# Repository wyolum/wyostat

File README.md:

# wyostat
Open source thermostat

* install node-red
           * https://nodered.org/docs/hardware/raspberrypi
* install node-red-dashboard
   	   * (from the ~/.node-red)
	   * https://flows.nodered.org/node/node-red-dashboard
* install node-red start up trigger: npm install node-red-contrib-startup-trigger
* install mosquitto (steps 1 & 2
           *https://learn.adafruit.com/diy-esp8266-home-security-with-lua-and-mqtt/configuring-mqtt-on-the-raspberry-pi)
* start node-red (from the command-line type $node-red)
* start mosquitto (from the command line type $moquitto)
* edit OpenThermostat.json from within node-red (update mqtt-broker ip address)
* deploy OpenThermostat.json from within node-red (update mqtt-broker ip address)
* Copy and edit arduino/OpenThermostat/README to arduino/OpenThermostat/config.h
* upload OpenThermostat.ino

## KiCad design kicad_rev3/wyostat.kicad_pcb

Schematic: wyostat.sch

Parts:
C1, C3, C5: 10nF,120V; C_1210
C7: 100nF; C_0805
C9: 100nF,100V; C_0805
C10: 100uF,50V; CP_Elec_10x10
C11: 2.2uF,50V; C_0805
C12: 1uF; C_0805
C13: 3.3nF; C_0805
C14: 10uF; C_0805
C15: 4.7uF; C_0805
D1, D2, D3: LED; LED_0603
D4: DiodeBridge; Diode_bridge
D5: CDSOD323-T05L; D_SOD-323_HandSoldering
F1: Polyfuse; Fuse_SMD2920
J1: 24 V AC IN; TerminalBlock_Pheonix_MPT-2.54mm_2pol
J2: OUT1; TerminalBlock_Pheonix_MPT-2.54mm_2pol
J3: OUT2; TerminalBlock_Pheonix_MPT-2.54mm_2pol
J4: OUT3; TerminalBlock_Pheonix_MPT-2.54mm_2pol
J5: I2C_ext1; Pin_Header_TMP102_1x06
J6: RH; pad_rect_smd
J7: RC; pad_rect_smd
J8: C; pad_rect_smd
J9: Y1; pad_rect_smd
J10: Y2; pad_rect_smd
J11: G; pad_rect_smd
J12: W1; pad_rect_smd
J13: USB_microAB; USB_Micro-B_Molex-105017-0001
J14: W2; pad_rect_smd
J15: Conn_Spare; TerminalBlock_Pheonix_MPT-2.54mm_3pol
J16: 5V_SEL; Pin_Header_Straight_1x04
JP1, JP2, JP3: LED_en; R_0805
JP4: GND; LED_0402
L1: 22uH; Inductor_ELL8TP
L2, L4: 330E; R_0805
Logo1: LOGO_WL; logo-WL3
Logo2: OSHW; logo-OSHW_6mm
Logo3: KiCad; logo-kicad_6mm_SilkScreen
Logo4: logo_snb; logo-skull_n_bones
Logo5: logo_warning; logo-warning
Q1, Q2, Q3: BTA204S; DPAK-2
R1, R5, R7, R12, R13, R17: 360; R_0805
R3, R9, R15: 200; R_0805
R4, R10, R16: 300; R_0805
R6, R11, R18: 39; R_0805
R19, R20, R21, R22: 10k; R_0805
R23, R24, R25: 0E; R_0805
S1: SW-ENTER; SW_SPST_FSM6JSMA
S2: SW-INC; SW_SPST_FSM6JSMA
S3: SW-DEC; SW_SPST_FSM6JSMA
S4: SW-MODE; SW_SPST_FSM6JSMA
SC1, SC2, SC3, SC4: SCREW; MountingHole_3.2mm_M3_Pad_Via
U1, U2, U3: MOC3063M; Optocoupler_6pin_smd
U4: Wemos-Lolin; Wemos_Lolin
U5: MAX17502FATB+T; TDFN-10

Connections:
/3V3: C7.2, J5.2, S1.1, S1.3, S2.1, S2.3, S3.1, S3.3, S4.2, S4.4, U4.13, U4.19; also elsewhere on the board
/5V: J16.2, J16.3, U4.16, U4.17
/5V_EXT: C14.1, J16.4, L1.2, U5.5
/5V_USB: C15.1, J16.1, L2.1
/24Vac-C: D4.3, J1.2, J2.2, J3.2, J4.2, J8.1
/24Vac-H: C1.2, C3.2, C5.2, F1.2, J1.1, J6.1, Q1.2 (T2), Q2.2 (T2), Q3.2 (T2), R1.2, R7.2, R13.2
/40VDC: C9.1, C10.1, C11.2, D4.1, U5.2, U5.3
/D+: J13.3, R24.2
/D-: J13.2, R23.2
/ID: J13.4, R25.2
/IN1: D1.1, U1.1, U4.24
/IN2: D2.1, U2.1, U4.25
/IN3: D3.1, U3.1, U4.2
/LX: L1.1, U5.10
/OUT1: J2.1, J9.1, Q1.1 (T1), R5.2, R6.1
/OUT2: J3.1, J11.1, Q2.1 (T1), R11.1, R12.2
/OUT3: J4.1, J12.1, Q3.1 (T1), R17.2, R18.1
/RC: J7.1, J15.2
/SCL: J5.4, U4.4; also elsewhere on the board
/SDA: J5.3, U4.3; also elsewhere on the board
/SS: C13.2, U5.6
/SW_D: R21.1, S3.2, S3.4, U4.8
/SW_E: R19.1, S1.2, S1.4, U4.9
/SW_I: R20.1, S2.2, S2.4, U4.10
/SW_M: R22.1, S4.1, S4.3, U4.7
/USB+: D5.1 (K), J13.1, L2.2
/VCC: C12.1, U5.4
/W2: J14.1, J15.1
/Y2: J10.1, J15.3
GND: C7.1, C9.2, C10.2, C11.1, C12.2, C13.1, C14.2, C15.2, D4.2, D5.2 (A), J5.1, J13.5, JP1.2, JP2.2, JP3.2, JP4.1, JP4.2, L4.2, R4.1, R10.1, R16.1, R19.2, R20.2, R21.2, R22.2, U4.14, U4.15, U4.18, U5.1, U5.9, U5.11; also elsewhere on the board
unnamed: C1.1, R6.2
unnamed: C3.1, R11.2
unnamed: C5.1, R18.2
unnamed: D1.2, R3.2
unnamed: D2.2, R9.2
unnamed: D3.2, R15.2
unnamed: D4.4, F1.1
unnamed: J13.S1, J13.S2, J13.S3, J13.S4, L4.1
unnamed: JP1.1, R3.1
unnamed: JP2.1, R9.1
unnamed: JP3.1, R15.1
unnamed: Q1.3 (G), R5.1, U1.4
unnamed: Q2.3 (G), R12.1, U2.4
unnamed: Q3.3 (G), R17.1, U3.4
unnamed: R1.1, U1.6
unnamed: R4.2, U1.2
unnamed: R7.1, U2.6
unnamed: R10.2, U2.2
unnamed: R13.1, U3.6
unnamed: R16.2, U3.2

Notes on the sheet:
Push Buttons
I2C interface for external connections to sensors etc. Sparkfun TMP102 breakout P/N : 13314 https://www.sparkfun.com/products/13314
I2C HEADER
TRIAC outputs
1.5V
Connect GNDREF to GND at VCC capacitor
AC-DC POWER SUPPLY
40 V AC MAX. ISOLATED
40 V AC MAX
INPUT POWER Input Power sources are : a. Micro USB 5V to Wemos Lolin b. 28 V AC to 5 V DC via switching regulator c. Micro USB on Wyostat (only Power, no Data) When using option "b" or "c", the micro USB cable MUST be removed to prevent power conflicts. When using option "a", the Power Selector Hea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
USB INPUT + REGULATOR
5mA
I2C RTC
24VAC MAX., ISOLATED DO NOT CONNECT 115VAC
USB OFF EXT
Extra connection pads brokenout to screw connector

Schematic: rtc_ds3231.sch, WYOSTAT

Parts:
BT1: Batt_RTC; CR2032_SMD2; Digikey BU2032SM-HD-GCT-ND
C8: 100nF; C_0805
R26, R27: 10k; R_0805
R28, R29: 4K7; R_0805
TP1: ~RST; Pin_Header_Straight_1x01
TP2: SQR; Pin_Header_Straight_1x01
TP3: 32kHz; Pin_Header_Straight_1x01
U6: DS3231N; DS3231

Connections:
/3V3: R26.1, R27.1, R28.2, R29.2, U6.2; also elsewhere on the board
/SCL: R28.1, U6.16; also elsewhere on the board
/SDA: R29.1, U6.15; also elsewhere on the board
/rtc_ds3231/32kHz: R27.2, TP3.1, U6.1
/rtc_ds3231/BAT: BT1.1, C8.1, U6.14
/rtc_ds3231/RESET: TP1.1, U6.4
/rtc_ds3231/SQR: R26.2, TP2.1, U6.3
GND: BT1.2, C8.2, U6.5, U6.6, U6.7, U6.8, U6.9, U6.10, U6.11, U6.12, U6.13; also elsewhere on the board

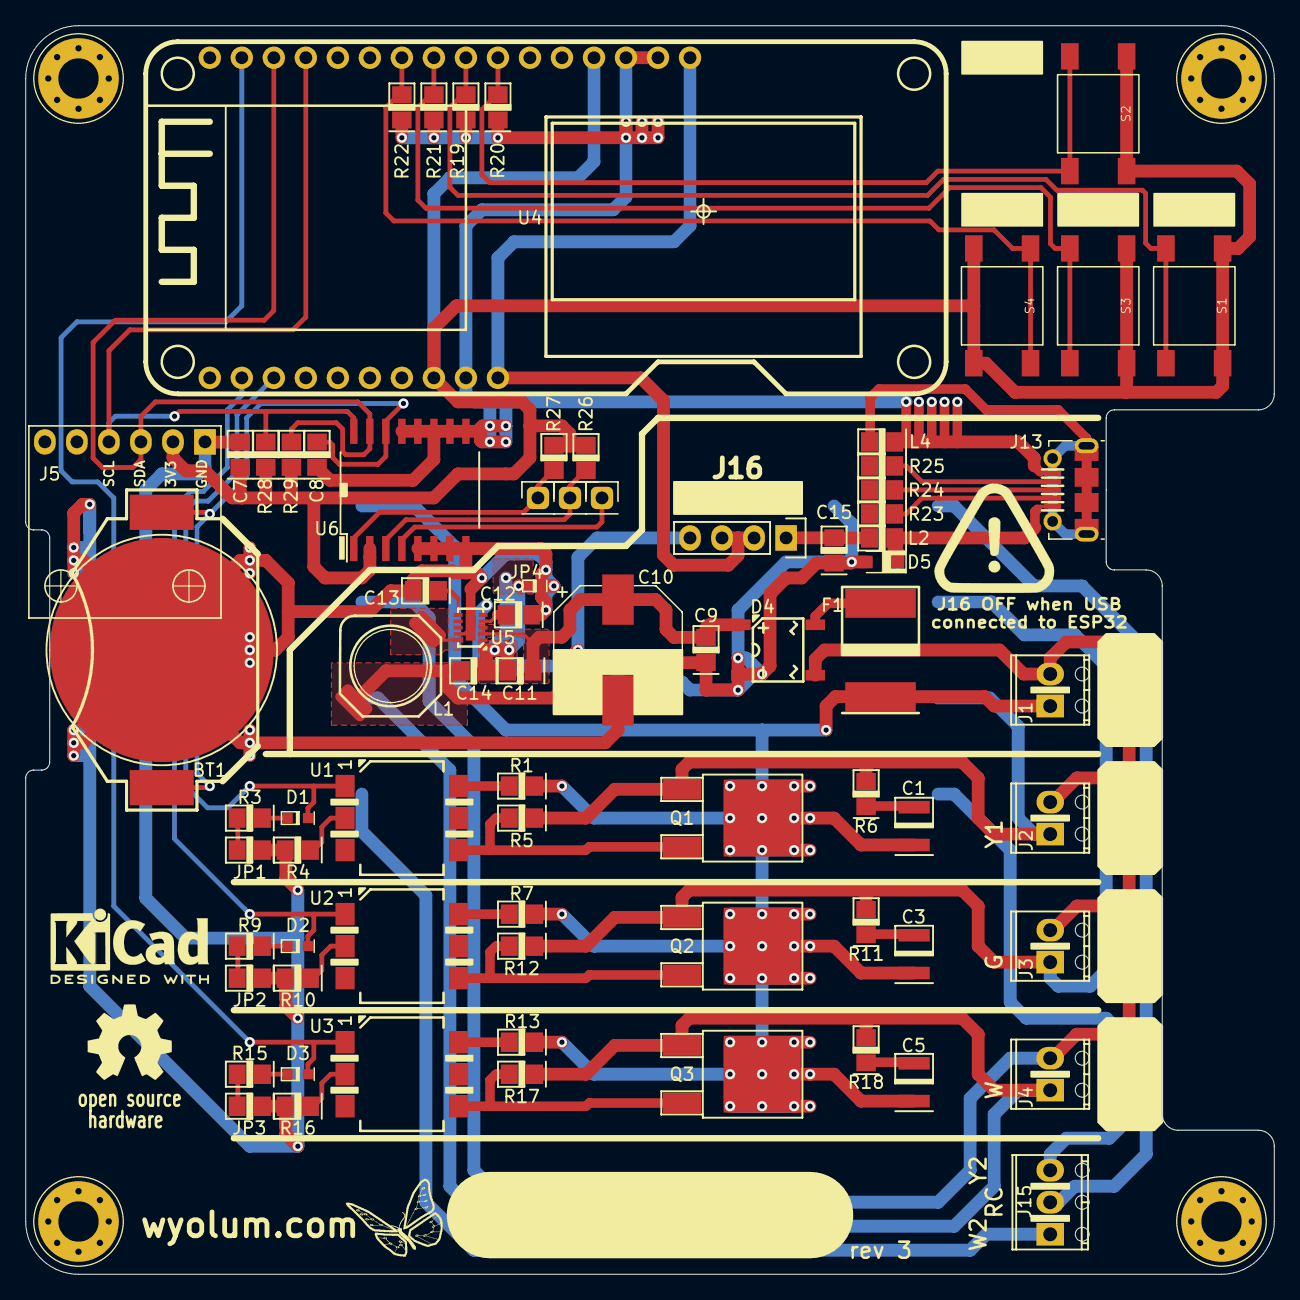
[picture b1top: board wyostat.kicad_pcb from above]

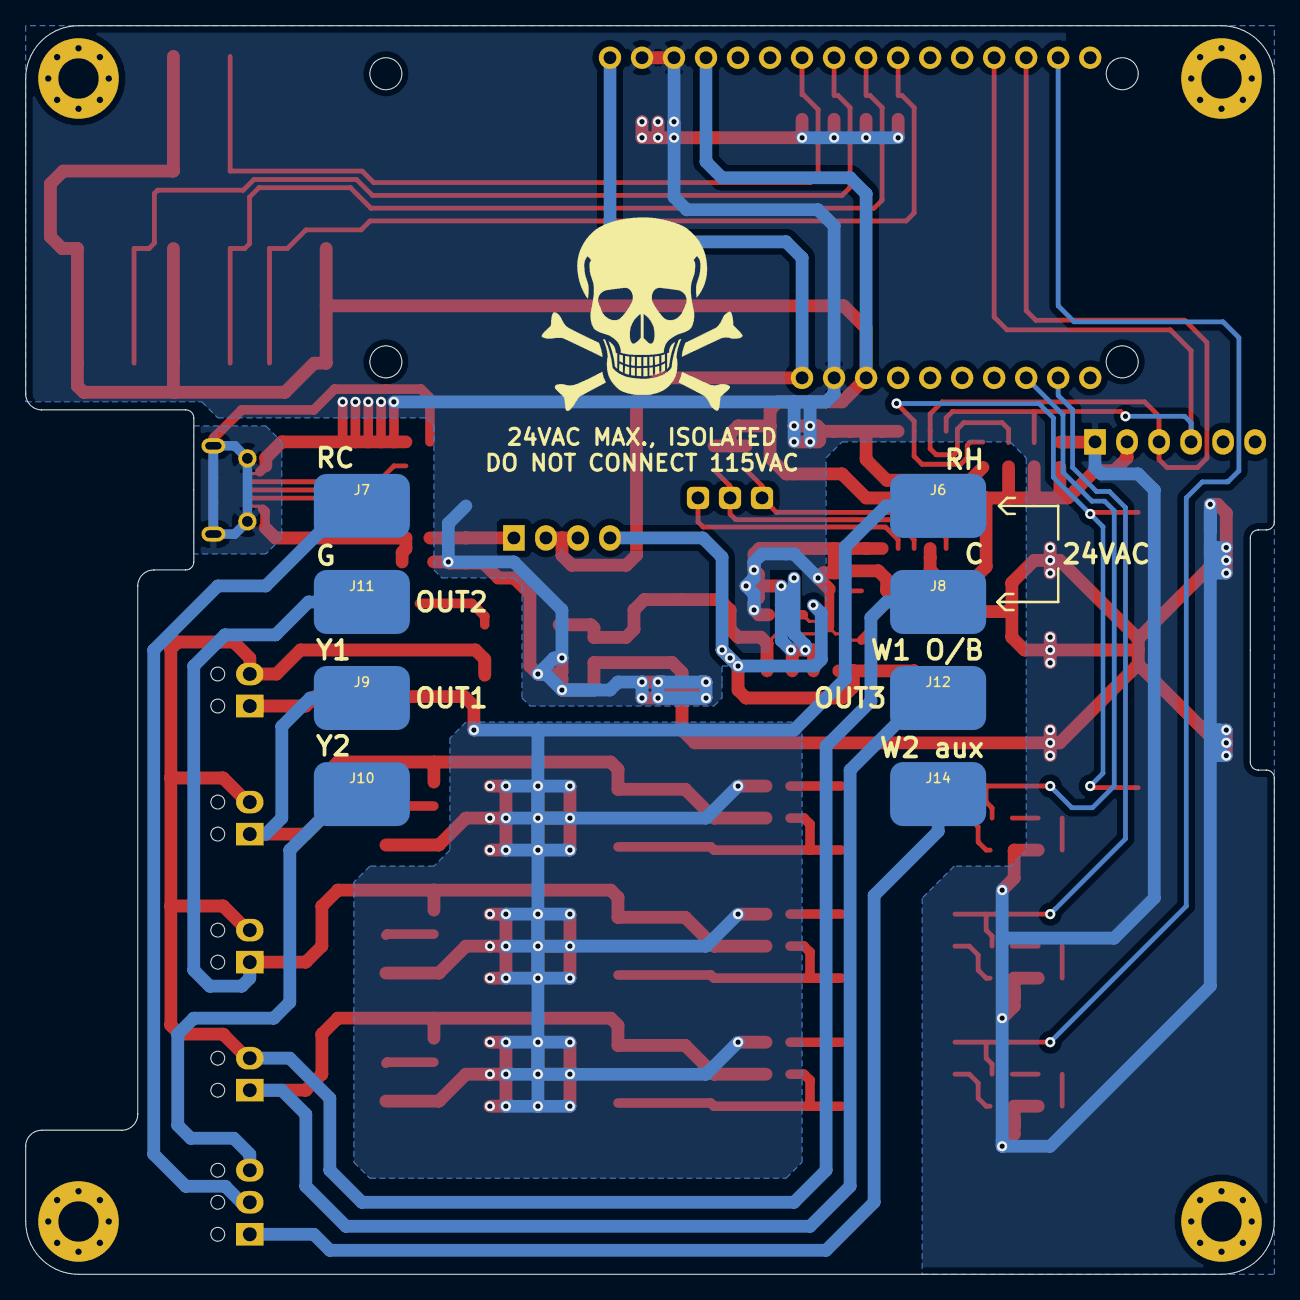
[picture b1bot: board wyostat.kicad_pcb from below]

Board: 2 copper layers, 99.1 x 99.1 mm, 93 parts (9 on the bottom side), 54 nets.

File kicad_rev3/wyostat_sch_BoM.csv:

Reference Type, Quantity, Reference, Value, Footprint, Datasheet, manf#, Field4, Field5, Field6, Field7, Field8, Field9, Field10, Field11, DNP, Digikey
"BT","1","BT1,","Batt_RTC","wyostat_fp:CR2032_SMD2","","mfr_pn","","","","","","","","","","BU2032SM-HD-GCT-ND "
"C","1","C13,","3.3nF","wyostat_fp:C_0805",""
"C","2","C7,C8,","100nF","wyostat_fp:C_0805",""
"C","1","C9,","100nF,100V","wyostat_fp:C_0805","","mfr_pn","","","","","","","","","",""
"C","3","C1,C3,C5,","10nF,120V","wyostat_fp:C_1210",""
"C","1","C12,","1uF","wyostat_fp:C_0805",""
"C","1","C15,","4.7uF","wyostat_fp:C_0805","","Value","","","","","","","","","",""
"C","1","C14,","10uF","wyostat_fp:C_0805",""
"C","1","C11,","2.2uF,50V","wyostat_fp:C_0805",""
"C","1","C10,","100uF,50V","wyostat_fp:CP_Elec_10x10",""
"D","1","D5,","CDSOD323-T05L","wyostat_fp:D_SOD-323_HandSoldering",""
"D","1","D4,","DiodeBridge","wyostat_fp:Diode_bridge",""
"D","3","D1,D2,D3,","LED","wyostat_fp:LED_0603","","","LED SS 5MM 625NM RED DIFF","2V, 10mA","Round with Domed Top, 5mm, T-1 3/4","Kingbright Corp","WP7113ID","Digikey","754-1264-ND","http://www.digikey.com/product-detail/en/WP7113ID/754-1264-N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","",""
"F","1","F1,","Polyfuse","wyostat_fp:Fuse_SMD2920",""
"J","1","J1,","24 V AC IN","wyostat_fp:TerminalBlock_Pheonix_MPT-2.54mm_2pol","","Value","","","","","","","","","",""
"J","1","J8,","C","wyostat_fp:pad_rect_smd",""
"J","1","J15,","Conn_Spare","wyostat_fp:TerminalBlock_Pheonix_MPT-2.54mm_3pol",""
"J","1","J11,","G","wyostat_fp:pad_rect_smd",""
"J","1","J5,","I2C_ext1","wyostat_fp:Pin_Header_Straight_1x04",""
"J","1","J2,","OUT1","wyostat_fp:TerminalBlock_Pheonix_MPT-2.54mm_2pol","","Value","","","","","","","","","",""
"J","1","J3,","OUT2","wyostat_fp:TerminalBlock_Pheonix_MPT-2.54mm_2pol","","Value","","","","","","","","","",""
"J","1","J4,","OUT3","wyostat_fp:TerminalBlock_Pheonix_MPT-2.54mm_2pol","","Value","","","","","","","","","",""
"J","1","J7,","RC","wyostat_fp:pad_rect_smd",""
"J","1","J6,","RH","wyostat_fp:pad_rect_smd",""
"J","1","J13,","USB_microAB","wyostat_fp:USB_Micro-B_Molex-105017-0001","","Value","","","","","","","","","",""
"J","1","J16,","5V_SEL","wyostat_fp:Pin_Header_Straight_1x04",""
"J","1","J12,","W1","wyostat_fp:pad_rect_smd",""
"J","1","J14,","W2","wyostat_fp:pad_rect_smd",""
"J","1","J9,","Y1","wyostat_fp:pad_rect_smd",""
"J","1","J10,","Y2","wyostat_fp:pad_rect_smd",""
"JP","1","JP4,","GND","wyostat_fp:LED_0402",""
"JP","3","JP1,JP2,JP3,","LED_en","wyostat_fp:R_0805",""
"L","2","L4,L2,","330E","wyostat_fp:R_0805","","Value","","","","","","","","","",""
"L","1","L1,","22uH","wyostat_fp:Inductor_ELL8TP","","mfr_pn","","","","","","","","","",""
"Logo","1","Logo3,","KiCad","wyostat_fp:logo-kicad_6mm_SilkScreen","","Value","","","","","","","","","",""
"Logo","1","Logo1,","LOGO_WL","wyostat_fp:logo-WL3","","Value","","","","","","","","","",""
"Logo","1","Logo2,","OSHW","wyostat_fp:logo-OSHW_6mm","","Value","","","","","","","","","",""
"Logo","1","Logo4,","logo_snb","wyostat_fp:logo-skull_n_bones","","Value","","","","","","","","","",""
"Logo","1","Logo5,","logo_warning","wyostat_fp:logo-warning","","Value","","","","","","","","","",""
"Q","3","Q1,Q2,Q3,","BTA204S","wyostat_fp:DPAK-2",""
"R","3","R6,R11,R18,","39","wyostat_fp:R_0805","","Value","","","","","","","","","-",""
"R","3","R3,R9,R15,","200","wyostat_fp:R_0805","","Value","","","","","","","","","",""
"R","3","R4,R10,R16,","300","wyostat_fp:R_0805","","Value","","","","","","","","","",""
"R","6","R1,R7,R13,R5,R12,R17,","360","wyostat_fp:R_0805","","Value","","","","","","","","","",""
"R","3","R23,R24,R25,","0E","wyostat_fp:R_0805","","Value","","","","","","","","","DNP",""
"R","2","R28,R29,","4K7","wyostat_fp:R_0805","","mfr_pn","","","","","","","","","",""
"R","6","R21,R22,R19,R20,R26,R27,","10k","wyostat_fp:R_0805",""
"S","1","S3,","SW-DEC","wyostat_fp:SW_SPST_FSM6JSMA",""
"S","1","S1,","SW-ENTER","wyostat_fp:SW_SPST_FSM6JSMA",""
"S","1","S2,","SW-INC","wyostat_fp:SW_SPST_FSM6JSMA",""
"S","1","S4,","SW-MODE","wyostat_fp:SW_SPST_FSM6JSMA",""
"SC","4","SC1,SC2,SC3,SC4,","SCREW","wyostat_fp:MountingHole_3.2mm_M3_Pad_Via",""
"TP","1","TP2,","SQR","wyostat_fp:Pin_Header_Straight_1x01","","mfr_pn","","","","","","","","","",""
"TP","1","TP3,","32kHz","wyostat_fp:Pin_Header_Straight_1x01","","mfr_pn","","","","","","","","","",""
"TP","1","TP1,","~RST","wyostat_fp:Pin_Header_Straight_1x01","","mfr_pn","","","","","","","","","",""
"U","1","U6,","DS3231N","wyostat_fp:DS3231","","mfr_pn","","","","","","","","","",""
"U","1","U5,","MAX17502FATB+T","wyostat_fp:TDFN-10","","mfr_pn","","","","","","","","","",""
"U","3","U1,U2,U3,","MOC3063M","wyostat_fp:Optocoupler_6pin_smd",""
"U","1","U4,","Wemos-Lolin","wyostat_fp:Wemos_Lolin",""

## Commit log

2017-10-19 change update rate for temp
2017-12-30 remove static copy of esp32 files
2017-12-30 try to checkin all the hardware files we need
2017-12-30 add back tools from .gitignore
2017-12-31 add prototype bom
2018-01-04 added settemperature to EEPROM
2018-02-08 add readme for config.h
2018-02-08 add config.h to gitignore
2018-02-08 try again
2018-03-12 initial kicad setup kicad
2018-03-12 kicad schematic, WIP
2018-03-13 schematic WIP
2018-03-15 layou, WIP
2018-03-15 kicad PCB, WIP
2018-03-16 kicad PCB, track layout
2018-03-17 PCB layout, WIP
2018-03-18 initial board layout
2018-03-19 adding pads for spring contacts
2018-03-19 Gerbers ready for OSHpark
2018-03-20 increased clearances, added inverse text
2018-03-20 added gerber zip
2018-03-20 improved silk legend
2018-03-21 cleanup
2018-03-22 trying out an enclosure/front cover plate
2018-03-23 enclosure, WIP
2018-03-24 modified contact pad positions
2018-03-24 enclosure WIP
2018-03-24 enclosure, first version, STL
2018-03-24 enclosure, buttons
2018-03-25 revised Butons STL
2018-03-26 modified Paste layer. Fixed Coin Cell footprint
2018-04-04 footprint corrections on PCB
2018-04-04 add RTC support, and basic buton handling
2018-04-05 PCB updated for 2nd round of prototype
2018-04-05 added Sparkfun TMP102 footprint and PCB edges modified
2018-04-06 3D printed case - added opening for temp sensor
2018-06-11 prettified silk legend
2018-06-13 prettified
2018-06-13 added details to Fabricate layer for assembly guide
2018-07-29 Added lo and hi settings for temperature control to allow control of AC and Furnace
2018-08-05 add esp32 mqtt example
2018-08-07 added wyostat messages to mqtt example
2018-08-07 added callback infrastructure
2018-08-07 minor refactor
2018-08-12 Added graphical themostat conroller from node-red
2018-08-17 basic thermostat w/o time functions
2018-08-21 Added Node-red lib
2018-08-21 added install notes to README
2018-08-29 minor mods
2018-09-02 added rev4 KiCAD folder, WIP
2018-11-19 testing display... not working
2018-11-20 add wifimanager
2018-11-20 debuggin display sensor compatibility
2018-11-21 added simple thermometer demo DisplayTemp
2018-11-22 test update
2018-11-22 re-compiled on Linux... using arduino 1.8.7, new libs seem required
2018-11-22 got temp to read by waking sensor prior to each read
2022-02-13 updated Temp102 code from SparkFun
2022-02-15 adding wyolum time service, getting compile errors
2022-02-15 TroubleShooting
2022-02-15 added config.h
2022-02-27 temp smoothing debugging
2022-02-27 added flow graph for node red
